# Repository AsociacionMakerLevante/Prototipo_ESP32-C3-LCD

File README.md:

# Prototipo_ESP32-C3-LCD
Archivos del prorotipo de la placa para el taller de FreeRTOS, es un diseño rápido con componentes que tenía a mano.. 

Código de prueba para verificar el Hardware, no usar el código como referencia!

No se han medido las señales de la placa con el osciloscopio, por lo que aún está por verificar el correcto funcionamiento del pcb a nivel de señal y consumos de corriente (medir corriente máxima que puede dar el LDO), a nivel de funcionalidad-programación parece correcto.

Cambios hardware para futuras revisiones:
- Condensadores y diodos TVS a la entrada del USB, ver compatibilidad con distintas marcas de cargadores.
- Cambiar la ubicación del sensor de temperatura (se calienta con la batería en carga) y aplicarle un "moat".
- Reducir espacios en las DRC e incrementar algunos planos de disipación térmica (considerar planos de tierra en las capas exteriores).
- Calcular y ajustar los condensadores (2*(Cl-Cs)) del cristal del RTC, medir la desviación de este.
- Reducir el número de valores distintos de resistencias y condensadores en el BOM.
- Mejoras EMI/EMC: filtro pi delante del diodo a continuación del USB, reducir ramificaciones (conexiones punto a punto), stitching vias perímetro, reubicar algunos componentes.

Es un diseño hardware MUY rápido para evaluar la herramienta de KiCad, en ningún caso usar como referencia. 

Si el proyecto tiene interés entre los asistentes a las reuniones de la asociación, se hará una revisión del PCB más despacio: mejorando el esquemático, el ruteado del PCB y buscando optimizar el consumo de corriente seleccionando los distintos componentes de la placa (cuando hay batería cada uA cuenta!).

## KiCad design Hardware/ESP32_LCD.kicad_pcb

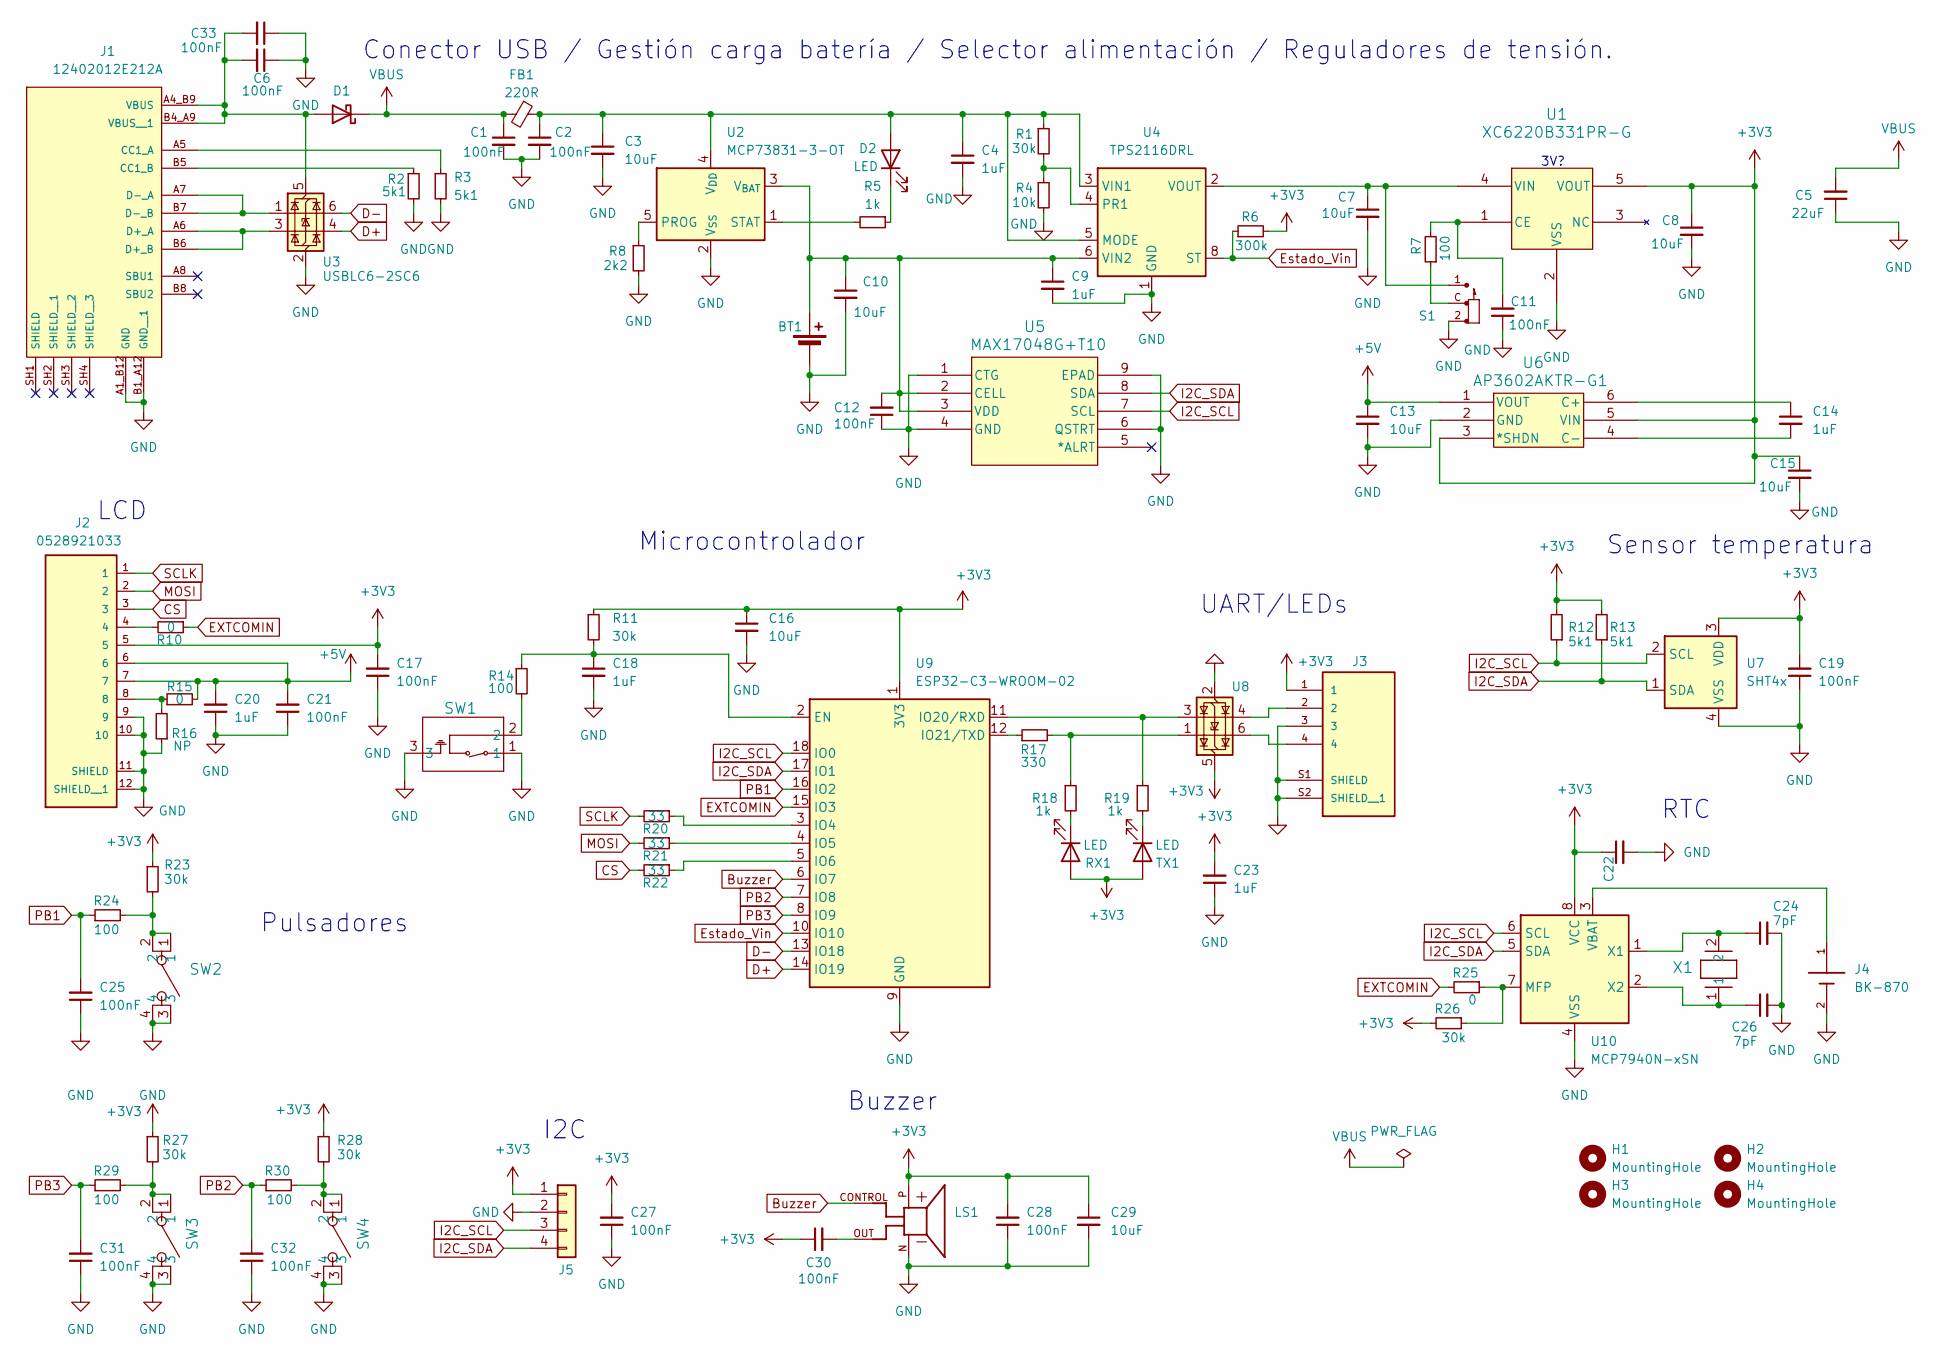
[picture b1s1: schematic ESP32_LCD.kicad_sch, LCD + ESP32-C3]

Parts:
BT1: Battery_Cell; JST_PH_S2B-PH-SM4-TB_1x02-1MP_P2.00mm_Horizontal
C1, C2, C6, C11, C12, C19, C25, C27, C28, C30, C31, C32, C33: 100nF; C_0603_1608Metric
C3, C7, C8, C10, C13, C15, C16, C22: 10uF; C_0603_1608Metric
C4, C9, C14, C23: 1uF; C_0603_1608Metric
C5: 22uF; CAP_UWF_5X5P4_NCH
C17, C21: 100nF; C_0402_1005Metric
C18: 1uF; C_0402_1005Metric_Pad0.74x0.62mm_HandSolder
C20: 1uF; C_0402_1005Metric
C24, C26: 7pF; C_0603_1608Metric
C29: 10uF; C_0603_1608Metric_Pad1.08x0.95mm_HandSolder
D1: 1N5819; D_SMA
D2: LED; LED_0603_1608Metric
FB1: 220R; R_0603_1608Metric
H1, H2, H3, H4: MountingHole; MountingHole_2.2mm_M2_ISO14580
J1: 12402012E212A; AMPHENOL_12402012E212A; PARTREV 4
J2: 0528921033; MOLEX_0528921033
J3: 0532610471; MOLEX_0532610471; PARTREV J
J4: BK-870; MPD_BK-870; PARTREV D
J5: Conn_01x04; PinHeader_1x04_P2.54mm_Vertical
LS1: CMI-8536-82-SMT-TR; PARTREV 1.01
R1, R23, R26, R27, R28: 30k; R_0603_1608Metric
R2, R3, R12, R13: 5k1; R_0603_1608Metric
R4: 10k; R_0603_1608Metric
R5, R18, R19: 1k; R_0603_1608Metric
R6: 300k; R_0603_1608Metric
R7, R14, R24, R29, R30: 100; R_0603_1608Metric
R8: 2k2; R_0603_1608Metric
R10, R15, R25: 0; R_0603_1608Metric
R11: 30k; R_0402_1005Metric_Pad0.72x0.64mm_HandSolder
R16: NP; R_0603_1608Metric
R17: 330; R_0603_1608Metric
R20, R21, R22: 33; R_0402_1005Metric_Pad0.72x0.64mm_HandSolder
RX1: LED; LED_0603_1608Metric
S1: SSAJ110100; SW_SSAJ110100; PARTREV N/A
SW1: B3U-1100P-B; B3U-1100P-B_OMR
SW2, SW3, SW4: 1825910-6; SW4_1825910-B_TEC
TX1: LED; LED_0603_1608Metric
U1: XC6220B331PR-G; SOT-89-5_TOR
U2: MCP73831-3-OT; SOT-23-5
U3, U8: USBLC6-2SC6; SOT-23-6
U4: TPS2116DRL; SOT-583-8
U5: MAX17048G+T10; 21-0168E_T822-3_MXM
U6: AP3602AKTR-G1; SOT-23-6_DIO
U7: SHT4x; Sensirion_DFN-4_1.5x1.5mm_P0.8mm_SHT4x_NoCentralPad
U9: ESP32-C3-WROOM-02
U10: MCP7940N-xSN; SOIC-8_3.9x4.9mm_P1.27mm
X1: CM8V-T1A-32.768KHZ-7PF-20PPM-TA-QC; CRYSTAL_CM8V-T1A-32.768KHZ-7PF-20PPM-TA-QC_MCX-L

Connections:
+3V3: C8.1, C15.1, C16.1, C17.2, C19.2, C22.1, C23.2, C27.2, C28.2, C29.1, C30.1, J2.5, J3.1, J5.1, LS1.P, R6.2, R11.1, R12.2, R13.2, R23.1, R26.2, R27.1, R28.1, RX1.2 (A), TX1.2 (A), U1.5 (VOUT), U6.3 (*SHDN), U6.5 (VIN), U7.3 (VDD), U8.5 (VBUS), U9.1 (3V3), U10.8 (VCC)
+5V: C13.1, C20.2, C21.2, J2.6, J2.7, R15.2, U6.1 (VOUT)
Buzzer: LS1.CONTROL, U9.6 (IO7)
CS: J2.3, R22.2
D+: U3.4 (I/O2), U9.14 (IO19)
D-: U3.6 (I/O1), U9.13 (IO18)
EXTCOMIN: R10.1, R25.2, U9.15 (IO3)
Estado_Vin: R6.1, U4.8 (ST), U9.10 (IO10)
GND: BT1.2 (-), C1.2, C2.2, C3.2, C4.2, C5.1, C6.1, C7.2, C8.2, C9.2, C10.2, C11.1, C12.1, C13.2, C15.2, C16.2, C17.1, C18.2, C19.1, C20.1, C21.1, C22.2, C23.1, C24.2, C25.1, C26.2, C27.1, C28.1, C29.2, C31.1, C32.1, C33.1, J1.A1_B12 (GND), J1.B1_A12 (GND__1), J2.9, J2.10, J2.11 (SHIELD), J2.12 (SHIELD__1), J3.3, J3.S1 (SHIELD), J3.S2 (SHIELD__1), J4.2, J5.2, LS1.N, R2.2, R3.2, R4.2, R8.2, R16.1, S1.2, SW1.1, SW1.3, SW2.3, SW2.4, SW3.3, SW3.4, SW4.3, SW4.4, U1.2 (VSS), U2.2 (V_{SS}), U3.2 (GND), U4.1 (GND), U5.1 (CTG), U5.4 (GND), U5.6 (QSTRT), U5.9 (EPAD), U6.2 (GND), U7.4 (VSS), U8.2 (GND), U9.9 (GND), U9.19 (GND), U10.4 (VSS)
I2C_SCL: J5.3, R12.1, U5.7 (SCL), U7.2 (SCL), U9.18 (IO0), U10.6 (SCL)
I2C_SDA: J5.4, R13.1, U5.8 (SDA), U7.1 (SDA), U9.17 (IO1), U10.5 (SDA)
MOSI: J2.2, R21.2
unnamed: BT1.1 (+), C9.1, C10.1, C12.2, U2.3 (V_{BAT}), U4.6 (VIN2), U5.2 (CELL), U5.3 (VDD)
unnamed: C30.2, LS1.OUT
unnamed: C6.2, C33.2, D1.2 (A), J1.A4_B9 (VBUS), J1.B4_A9 (VBUS__1), U3.5 (VBUS)
unnamed: C2.1, C3.1, C4.1, D2.2 (A), FB1.1, R1.1, U2.4 (V_{DD}), U4.3 (VIN1), U4.5 (MODE)
unnamed: D2.1 (K), R5.1
unnamed: J1.A5 (CC1_A), R3.1
unnamed: J1.B5 (CC1_B), R2.1
unnamed: J1.A6 (D+_A), J1.B6 (D+_B), U3.3 (I/O2)
unnamed: J1.A7 (D-_A), J1.B7 (D-_B), U3.1 (I/O1)
unnamed: J2.4, R10.2
unnamed: J2.8, R15.1, R16.2
unnamed: J3.2, U8.4 (I/O2)
unnamed: J3.4, U8.6 (I/O1)
unnamed: R7.1, S1.C
unnamed: R14.2, SW1.2
unnamed: R17.2, R18.1, U8.1 (I/O1)
unnamed: R23.2, R24.2, SW2.1, SW2.2
unnamed: R27.2, R29.2, SW3.1, SW3.2
unnamed: R28.2, R30.2, SW4.1, SW4.2
unnamed: R18.2, RX1.1 (K)
unnamed: R19.2, TX1.1 (K)
unnamed: C11.2, R7.2, U1.1 (CE)
unnamed: C7.1, S1.1, U1.4 (VIN), U4.2 (VOUT), U4.7 (VOUT)
unnamed: R8.1, U2.5 (PROG)
unnamed: R5.2, U2.1 (STAT)
unnamed: R1.2, R4.1, U4.4 (PR1)
unnamed: C14.1, U6.6 (C+)
unnamed: C14.2, U6.4 (C-)
unnamed: C18.1, R11.2, R14.1, U9.2 (EN)
unnamed: R20.1, U9.3 (IO4)
unnamed: R21.1, U9.4 (IO5)
unnamed: R22.1, U9.5 (IO6)
unnamed: R19.1, U8.3 (I/O2), U9.11 (IO20/RXD)
unnamed: R17.1, U9.12 (IO21/TXD)
unnamed: R25.1, R26.1, U10.7 (MFP)
unnamed: J4.1, U10.3 (VBAT)
unnamed: C24.1, U10.1 (X1), X1.2
unnamed: C26.1, U10.2 (X2), X1.1
PB1: C25.2, R24.1, U9.16 (IO2)
PB2: C32.2, R30.1, U9.7 (IO8)
PB3: C31.2, R29.1, U9.8 (IO9)
SCLK: J2.1, R20.2
VBUS: C1.1, C5.2, D1.1 (K), FB1.2

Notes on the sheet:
Sensor temperatura
UART/LEDs
Conector USB / Gestión carga batería / Selector alimentación / Reguladores de tensión.
LCD
3V?
Pulsadores
Microcontrolador
Buzzer
RTC
I2C

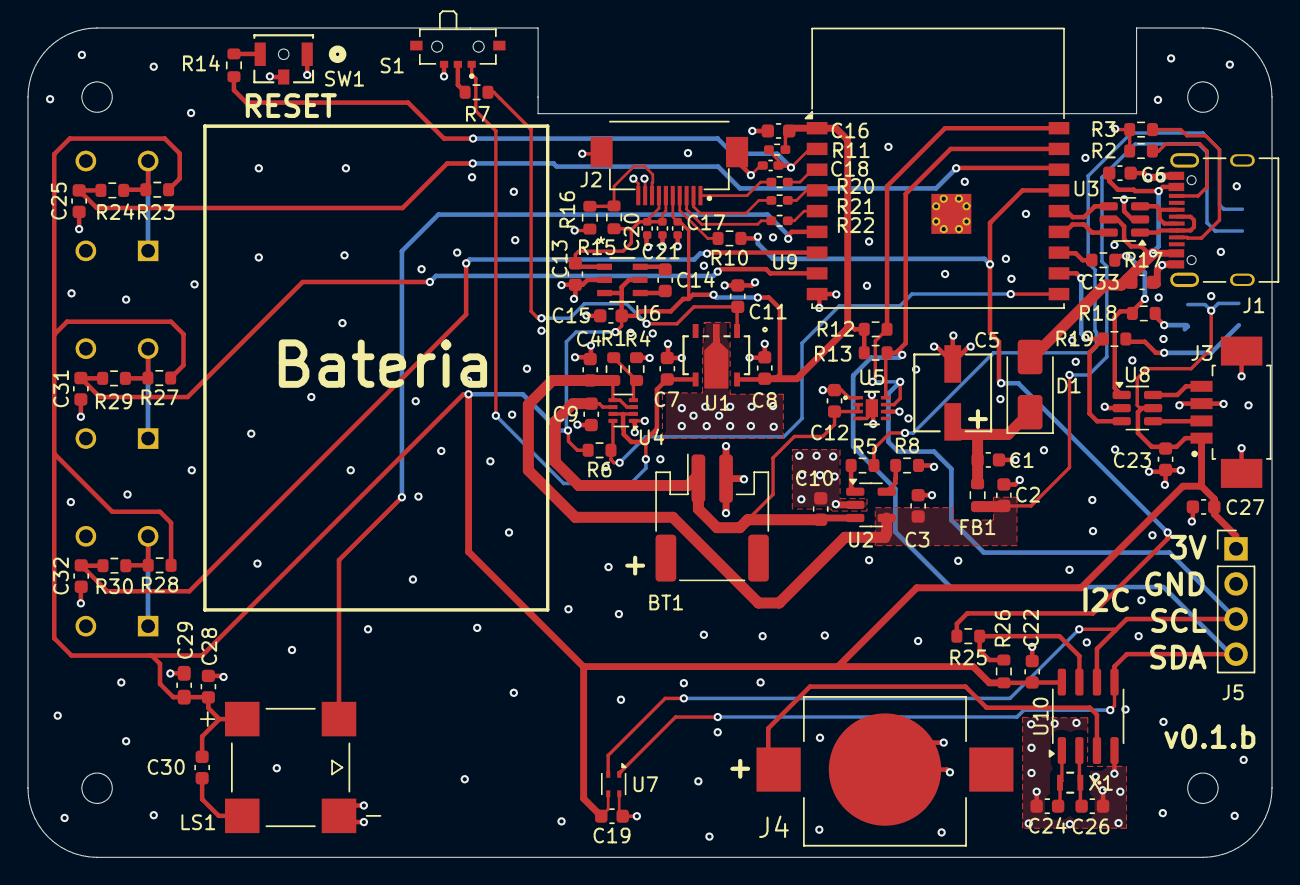
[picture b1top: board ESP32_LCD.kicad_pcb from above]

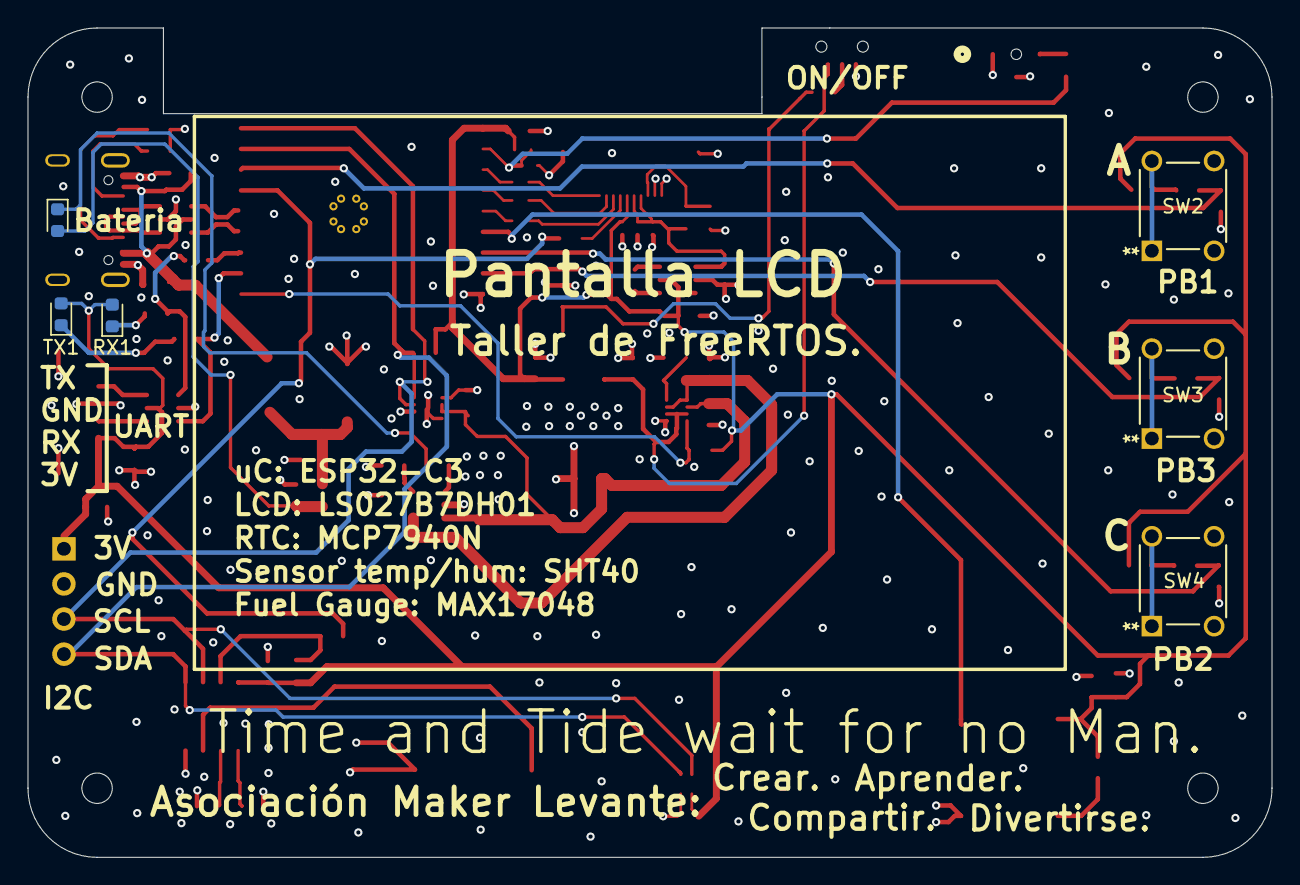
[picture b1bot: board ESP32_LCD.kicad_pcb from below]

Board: 4 copper layers, 90.0 x 60.0 mm, 94 parts (6 on the bottom side), 55 nets.
